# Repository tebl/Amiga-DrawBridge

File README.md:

# Amiga DrawBridge and Greaseweazle
I started this project out of fascination after reading a series of articles written by Rob Smith for the Amiga Addict magazine, detailing his solution for reading and writing Amiga floppy disks using an Arduino. Many of the build-yourself solutions provided came with some caveats, so I tried to look for the combination that should be the easiest to assemble. Along the way I also learned about some of the other well known solutions, in particular the Greaseweazle created by Keir Fraser. While there are certainly more professional options available on the market, KryoFlux in particular comes to mind. For the rest of us that want to make backups of our personal disks, I think that using these could be a fun little diversion into the world of backups.

- [1> Amiga DrawBridge](#1-amiga-drawbridge)
  - [1.1> Modules](#11-modules)
- [2> Greaseweazle](#2-greaseweazle)
  - [2.1> Modules](#21-modules)

## 1> Amiga DrawBridge
Rob Smith called his solution the **Arduino Amiga Floppy Disk Reader/Writer**, colloquially known as the **DrawBridge**. Completely open solution created with the Arduino as a starting point, all of the [information](http://amiga.robsmithdev.co.uk/instructions/promini) that you'd need to build it can be found on his [homepage](http://amiga.robsmithdev.co.uk/). You don't need more than few relatively common modules and a ton of wires to make it all work - so don't feel like this is something that you have to do in order to get started. These PCBs exists because I enjoy drawing things, and an inherent distrust of the kind of cheap Dupont cables I find myself purchasing. So I made a PCB for soldering the components onto instead.

One of the more interesting features of the DrawBridge is that he has put together a modified version of WinUAE, allowing the emulator to work directly with your physical disks! He later ported the feature so that the same can be done with the Greaseweazle, pretty impressive stuff!

### 1.1> Modules
For the technical details as well as information regarding the modules included by this specific github project, consult the table below - follow the documentation links for build instructions, BOM and anything else of that sort.  Faceplates and any backplates listed are mainly decorative, allowing you to put together something similar to a case without actually requiring a 3d-printer. 

| Module               | Required  | Documentation | Order      |
| -------------------- | --------- | ------------- | ---------- |
| Amiga DrawBridge     |       Yes | [Documentation](https://github.com/tebl/Amiga-DrawBridge/tree/main/Amiga%20Drawbridge), [Firmware](https://github.com/tebl/Amiga-DrawBridge/blob/main/documentation/drawbridge_firmware.md)                  | [PCBWay](https://www.pcbway.com/project/shareproject/Amiga_DrawBridge_fade665c.html)
| Amiga DrawBridge FA1 | Optional faceplate | [Documentation](https://github.com/tebl/Amiga-DrawBridge/tree/main/faceplates/Amiga%20Drawbridge%20FA1) | [PCBWay](https://www.pcbway.com/project/shareproject/Amiga_DrawBridge_Faceplate_FA1_f181f9af.html)
| Amiga DrawBridge FA2 | Optional faceplate | [Documentation](https://github.com/tebl/Amiga-DrawBridge/tree/main/faceplates/Amiga%20Drawbridge%20FA2) | [PCBWay](https://www.pcbway.com/project/shareproject/Amiga_DrawBridge_Faceplate_FA2_89c6eb36.html)
| Amiga DrawBridge BA1 | Optional backplate | [Documentation](https://github.com/tebl/Amiga-DrawBridge/tree/main/faceplates/Amiga%20Drawbridge%20BA1) | PCBWay

## 2> Greaseweazle
The [Greaseweazle](https://github.com/keirf/Greaseweazle) is another well known low-cost solution for working with physical floppy disks, having been created by Keir Fraser (also the creator of the FlashFloppy-firmware for *Gotek*-drives). The difference from the *DrawBridge* is that instead of working like a disk controller, it instead attempts to read the raw magnetic flux layer from the disks. This process *could* allow damaged or disks of unknown origin to be imaged.

### 2.1> Modules
For the technical details as well as information regarding the modules included by this specific github project, consult the table below - follow the documentation links for build instructions, BOM and anything else of that sort.  Faceplates and any backplates listed are mainly decorative, allowing you to put together something similar to a case without actually requiring a 3d-printer. 

| Module               | Required  | Documentation | Order      |
| -------------------- | --------- | ------------- | ---------- |
| Greaseweazle         |       Yes | [Documentation](https://github.com/tebl/Amiga-DrawBridge/tree/main/Greaseweazle), [Firmware](https://github.com/tebl/Amiga-DrawBridge/blob/main/documentation/greaseweazle_firmware.md), [Getting started](https://github.com/tebl/Amiga-DrawBridge/blob/main/documentation/greaseweazle_basics.md)                                                    | [PCBWay](https://www.pcbway.com/project/shareproject/Greaseweazle_0ea657b2.html)
| Greaseweazle FA1     | Optional faceplate | [Documentation](https://github.com/tebl/Amiga-DrawBridge/tree/main/faceplates/Greaseweazle%20FA1)       | [PCBWay](https://www.pcbway.com/project/shareproject/Greaseweazle_Faceplate_FA1_816b583d.html)
| Greaseweazle BA1 | Optional faceplate | [Documentation](https://github.com/tebl/Amiga-DrawBridge/tree/main/faceplates/Greaseweazle%20FB1)           | [PCBWay](https://www.pcbway.com/project/shareproject/Greaseweazle_Faceplate_FB1_83a3ce18.html)

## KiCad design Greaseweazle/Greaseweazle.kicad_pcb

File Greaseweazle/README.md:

# Greaseweazle
The [Greaseweazle](https://github.com/keirf/Greaseweazle) is a well known solution for working with physical floppy disks, all within the comforts of a modern operating system. It was created Keir Fraser, also the creator of the Flash Floppy firmware for Gotek drives, as a low cost alternative to the professional-oriented backup solutions such as the KryoFlux. Given that I've combined a project for creating both a DrawBridge and Greaseweazle into one, it is would be natural to say a few words about the differences between the two.

While *DrawBridge* was originally created to work with a specific disk format for the *Commodore Amiga*, the *Greaseweazle* will instead work with the raw magnetic flux layer from the disks. This may allow you to archive damaged, or even disks from unknown sources, to be archived for prosperity. Note that this does not necessarily mean you can use the resulting files, for that you would need a suitable emulator or similar program that have the capability of understanding the magnetic data that was originally read from the disks.

- [1> Building the device](#1-building-the-device)
  - [1.1> Soldering it together](#11-soldering-it-together)
  - [1.2> Power considerations](#12-power-considerations)
  - [1.3> Modifying STM32](#13-modifying-stm32)
  - [1.4> Let there be light](#14-let-there-be-light)
  - [1.5> Amstrad components](#15-amstrad-components)
  - [1.6> Finishing touches](#16-finishing-touches)
- [2> Schematic](#2-schematic)
- [3> BOM](#3-bom)

# 1> Building the device
Building a device such as this assumes you have at least minor experience soldering things together, recommended is that you at the very least have access to a soldering station with adjustable temperature. If currently available, you should probably start with 60/40 rosin core solder as the lead-free alternatives tends to be a bit harder to work with.

With the equipment sorted, now comes the shopping - so head on over to the [BOM](#3-bom)-section for some information on what kind of components that you'll need. Note that with sites such as ebay, AliExpress and similar sites that sell cheap chinese components, you'll need to treat these as a suggested search term and look for something that matches the gallery pictures.

## 1.1> Soldering it together
The construction of this unit should be fairly straight-forward, just take your time in order to make sure everything goes into place - more or less straight. I usually recommend starting by having a good look at the PCBs, try to figure out where all of the listed components go and in which orientation they go in (all of this should be clearly marked on the silkscreen). 

I will usually try to install components sorted by their physical size, doing it this way means you'll have an easier time keeping everything from looking somewhat crooked. This is your board, your build and you want it perfect - don't you? If you said no, then please go sit in a corner and think hard about your answer because I worked very hard at creating this design for myself and whoever wants one.

Here we've started by soldering all of the resistors, ensuring that we're using the correct values in each position. Note that some of the resistors will have a value printed with an asterisk after it, you may need to change these specific values or skip them entirely.

*) The value of these resistors need to be matched with the kind of LEDs that you are going to install on the board. The values as suggested should give a comfortably dimmed light when used with modern frosted LEDs, but need to be increased when used with bright clear LEDs. If you have access to the datasheet that goes with your LEDs and the maths to go with it, feel free to perform the necessary calculations. When in doubt you could always leave them out, then try out various values when testing a mostly completed unit.

**) This only applies to R10, not featured in the current pictures as it was added in a later revision. This is a convenient spot to install a new THT resistor in case you need to fix a specific cloned STM32 *Blue Pill*, as mentioned in the [Greaseweazle FAQ](https://github.com/keirf/Greaseweazle/wiki/Troubleshooting-FAQ) as a workaround for a board not showing up as a USB device. Unless you've specifically run into this issue, then you should **NOT** install R10.

Next step is installing the single transistor, as well as two of the resistors this will invert the activity LED so that it only lights up when there is traffic. While we can actually buy 2n3904 with legs pre-bent to match the footprint, these are very expensive and it is easier to just bend out the legs for these ourselves - taking care to match the flat side to that of the silkscreen. The reason for doing it this way is to make it easier to solder it in for beginners such as myself.

At this point we've gone ahead and installed the pin headers that will eventually be used to hold the STM32 board as well as a 34-pin IDC for the floppy drive itself. There's also a spot for a 26-pin version of it the interface for use with Amstrad 3" disk drives, but as I do not own any physical disks and/or disk drives I've not had to a chance to test this out for myself. Though I prefer the keying provided by the IDC sockets, you can instead opt to use standard dual-row pin headers here instead. 

## 1.2> Power considerations
Simple USB devices such as the various MCU boards are usually limited to a current draw of only **500mA**, plenty for doing small projects based on microcontrollers such as Arduino, STM32 and similar along with a handful of modern components. However in this case we'll be attempting to connect up a physical floppy drive up to the device and the powerdraw might easily surpass this, though this *might* be enough when used with later notebook-style disk drives. During my own testing with several older 3.5" floppy drives this was nowhere near enough, leading the drive to get stuck in a reset-loop.

For that reason, I'll be powering the drive separately using a DC 5v center positive power supply connected via the barrel connector. JP1 has been shorted across pins 1-2, this will separate this power supply from that of the USB (power LED will reflect that of the drive itself as these are now separate). 

The power cable going to the drive was bought ready-made as these are still available on sites such as Aliexpress and similar (usually listed as floppy power splitter or something to that effect), cutting off whatever parts I didn't need. Some floppy drives may also require 12v for such as many of the 5.25" drives and older, for those the recommended route is connecting one of the larger 4 pin Molex connector to J4 and power the whole thing from a PSU that delivers both of these voltages. An assembly picture for a later point in the build process is shown below.

If you buy one of the commonly available kit for connecting SATA/PATA drives up to a system over USB, you can get PSU that goes along with that. It's common for the cable to have a red wire for 5v, yellow for 12 and black for ground, but if you dug something really old out of a closet it might be a good idea to check the wiring as things wasn't always quite as standardized as it is now.

**WARNING!** The Amstrad 3-inch disk drives have the 5v and 12v wires swapped, connecting the drives to the floppy power connector as shown will instantly kill it. Have a read through of [1.5> Amstrad components](#15-amstrad-components) if you need to work with these drives, the short story is that you need to add a second modified power cable for these specific drives. 

## 1.3> Modifying STM32

This is more or less just a cosmetic thing, mainly because the boot jumpers on the standard *blue pill* make it a bit too tall to be used with a faceplate. Before we get too far ahead of ourselves and doing any actual work with the board, it might be wise to do some preliminary tests to make sure that the board you have is one of those that can be considered "*functional*" - because unfortunately there are quite a lot of boards that simply will not work properly! For that reason I suggest that you follow most of the [Greaseweazle Firmware](https://github.com/tebl/Amiga-DrawBridge/blob/main/documentation/greaseweazle_firmware.md) document, at least to ensure that it passes the "*blinky*"-test. 

Now that we've determined that we have a working board, we can get started on those modifications mentioned. If you have access to a desoldering station or simply a desoldering pump, you can just simply remove the 6pin header from the board and add a couple of pieces of wires in their place.

If you don't want to through the trouble of removing components, then an alternative is just to use a pair of pliers and pull off the plastic part of it (with a bit of force). Then cut off the part of the pins we don't need, either solder a piece of wire across the top as above to short them as expected - or you could just shorten the pins and bend them into contact with eachother, then add a bit of solder to ensure good contact.

When satisfied with the results, go ahead and solder the board into place on the main PCB.

## 1.4> Let there be light
Missing so far is the actual LEDs, which'll need a bit of vertical adjustment after installing some 10mm nylon hex standoffs. Your standard 5mm LEDs won't be quite that tall, so the suggestion is to put the LEDs into place (longer pin goes in the round hole) and then install the faceplate on top (without soldering any of the pins).

Start by soldering one of the pins, then reheat while pushing the LED firmly into the cutout on the faceplate. When satisfied that the results look good, you can solder the remaining pin as well as do a touch-up on the first one to ensure good connection. Shown below is where we should be at this point in the installation, keep on reading if you require support for 3 inch Amstrad drives as found on ZX Spectrum +3 and later Amstrad CPC computers (664 and 6128) - otherwise just skip ahead to [finishing touches](#16-finishing-touches).

## 1.5> Amstrad components
The Greaseweazle board also has a 26-pin option for connecting a 3 inch disk drive, commonly found installed in later Amstrad-produced machines such as the Sinclair ZX Spectrum +3, Amstrad CPC 664 and 6128 as well as some external disk disk drive options such as the FD-1 (needs to have internal power cable disconnected). All of these had single-sided drives, it is also the only configuration that I've had the chance to test.

Here we've gone ahead and installed the 26-pin connector as well as the 3-pin header, ensuring that we set it according to the type of drive we have available. The cable I'm using was ordered as a 26-pin ribbon cable off AliExpress without a cable twist, but before you can even consider connecting a drive up to the board we need to have a chat about safety.

**WARNING!** The Amstrad drives have a power connector that have been reversed, at least when compared to the later PC drives that we've become more familiar in the time since the 3 inch disk drives fell into obscurity (even though it shares the same connector). Connecting an unmodified floppy power connector into one of the drives will instantly kill your drive! 

To handle this you can consider just picking up a cheap splitter cable from AliExpress or similar sources, we'll then need to reverse the red and yellow cable on it - remembering to mark it specifically as being for Amstrad drives only. This is done by using a needle to slightly press in the little metal hooks on these two cables and pull out the cable, carefully bend the little hook back out again before reinserting the cable into the correct position [for Amstrad drives]. If you can't find a splitter with the male connector, you can always just split together two sets of cables when soldering them to the board - personally I prefer to have it detachable as this feature would rarely be used.

**NB!** As already mentioned in less than direct terms, I've not tested this solution with dual-sided drives. According to my mediocre Googling skills these drives were found on the Amstrad PCW line of computers, but as I lack a suitable drive and the corresponding disks to test things out I can't test it.

## 1.6> Finishing touches
If you still haven't installed the Greaseweazle firmware on the device, refer to [Greaseweazle Firmware](https://github.com/tebl/Amiga-DrawBridge/blob/main/documentation/greaseweazle_firmware.md) document for information on getting that done now. With the firmware in place, you can now finally connect up the drive and the device itself up to your computer using the Micro USB port (remember to power the drive via the barrel jack or molex, if needed).

The supplied software is easy to use for anyone with a passing familiarity with comand-line utilities, but I've put together a separate document on the [basics](https://github.com/tebl/Amiga-DrawBridge/blob/main/documentation/greaseweazle_basics.md) of actually using it.

# 2> Schematic
The supplied KiCad files should be sufficient as both a schematic and as a  starting point for ordering PCBs (basically you could just zip the contents of the export folder and upload that on a fabrication site), the schematic is also available in [PDF-format](https://github.com/tebl/Amiga-DrawBridge/tree/main/documentation/schematic) and this is what you'll need to print and work your way through this things don't work as expected after assembly.

# 3> BOM
Most parts should be easy to get a hold of from your favourite local electronic component shop, but given that I don't have access to such shops where I live so everything was based on whatever I could get cheapest from eBay/AliExpress (free shipping, but plan on waiting 3-4 weeks for delivery). Components in parenthesis can be considered optional for features beyond the more basic functionality, but where's the fun in that? You deserve the complete package.

| Reference             | Item                                                              | Count | Order  |
| --------------------- | ----------------------------------------------------------------- | ----- | ------ |
| Interface PCB         | Fabricate using Gerber files                                      |     1 | [PCBWay](https://www.pcbway.com/project/shareproject/Greaseweazle_0ea657b2.html)
| Faceplate PCB *       | Fabricate using Gerber files                                      |    (1)| [PCBWay](https://www.pcbway.com/project/shareproject/?tag=Greaseweazle%20Faceplates)
| A1                    | STM32F103C8T6 board (*blue pill*)                                 |     1 |
| D1,D2                 | 5mm LED, preferably one that is frosted                           |    (2)|
| J1 **                 | 2x17 pin male IDC socket                                          |     1 |
| J2                    | 2.1mm x 5.5mm barrel plug                                         |    (1)|
| J6 **                 | 2x13 pin male IDC socket                                          |    (1)|
| Q1                    | 2N3904 transistor (TO-92)                                         |    (2)|
| R1                    | 10k ohm resistor                                                  |    (1)|
| R2 ***                | 1k ohm resistor                                                   |    (1)|
| R3 ***                | 100 ohm resistor                                                  |    (1)|
| R4                    | 1k ohm resistor                                                   |    (1)|
| R5,R6,R7,R8           | 1k ohm resistor                                                   |     4 |
| R10 ****              | 1.5k ohm resistor (only install if explicitly need)               |    (1)|
| Mounting *****        | Nylon M3 hex standoffs 6mm (M-F)                                  |    (4)|
| Mounting *****        | Nylon M3 hex standoffs 8mm (M-F)                                  |    (4)|
| Mounting *****        | Nylon M3x6mm nylon screws                                         |    (4)|
| Floppy PSU cable      | 4 pin floppy connector with cable                                 |     1 |

*) Check out [faceplate](https://github.com/tebl/Amiga-DrawBridge/tree/main/faceplates) section of this repository or [PCBWay shared projects](https://www.pcbway.com/project/shareproject/?tag=Greaseweazle) for available options.

**) Components listed are for keyed IDC connector sockets, if you want to go with a cheaper option that is probably already in a box somewhere in your workshop - use standard dual-row pin breakable headers.

***) As detailed in the build notes, you may need to adjust these to match the type of LED you are installing. As long as you aren't installing the clear bright LEDs you should shouldn't have to change these except for preferences. Do the math if you have the correct datasheets and know how to do them, I find it easier to just throw something in there and see what happens.

****) Footprint for R10 provided as a spot for installing new resistor if the specific *Blue Pill* clone needs it and the original has been removed from the board, consult [Greaseweazle FAQ](https://github.com/keirf/Greaseweazle/wiki/Troubleshooting-FAQ) for more information. If unsure, do **NOT** install it.

*****) These are used in various places of the project. You can usually find some kits for M3 nylon standoffs, for the 6mm hex standoffs used on the bottom I've just cut off the screw part of it.

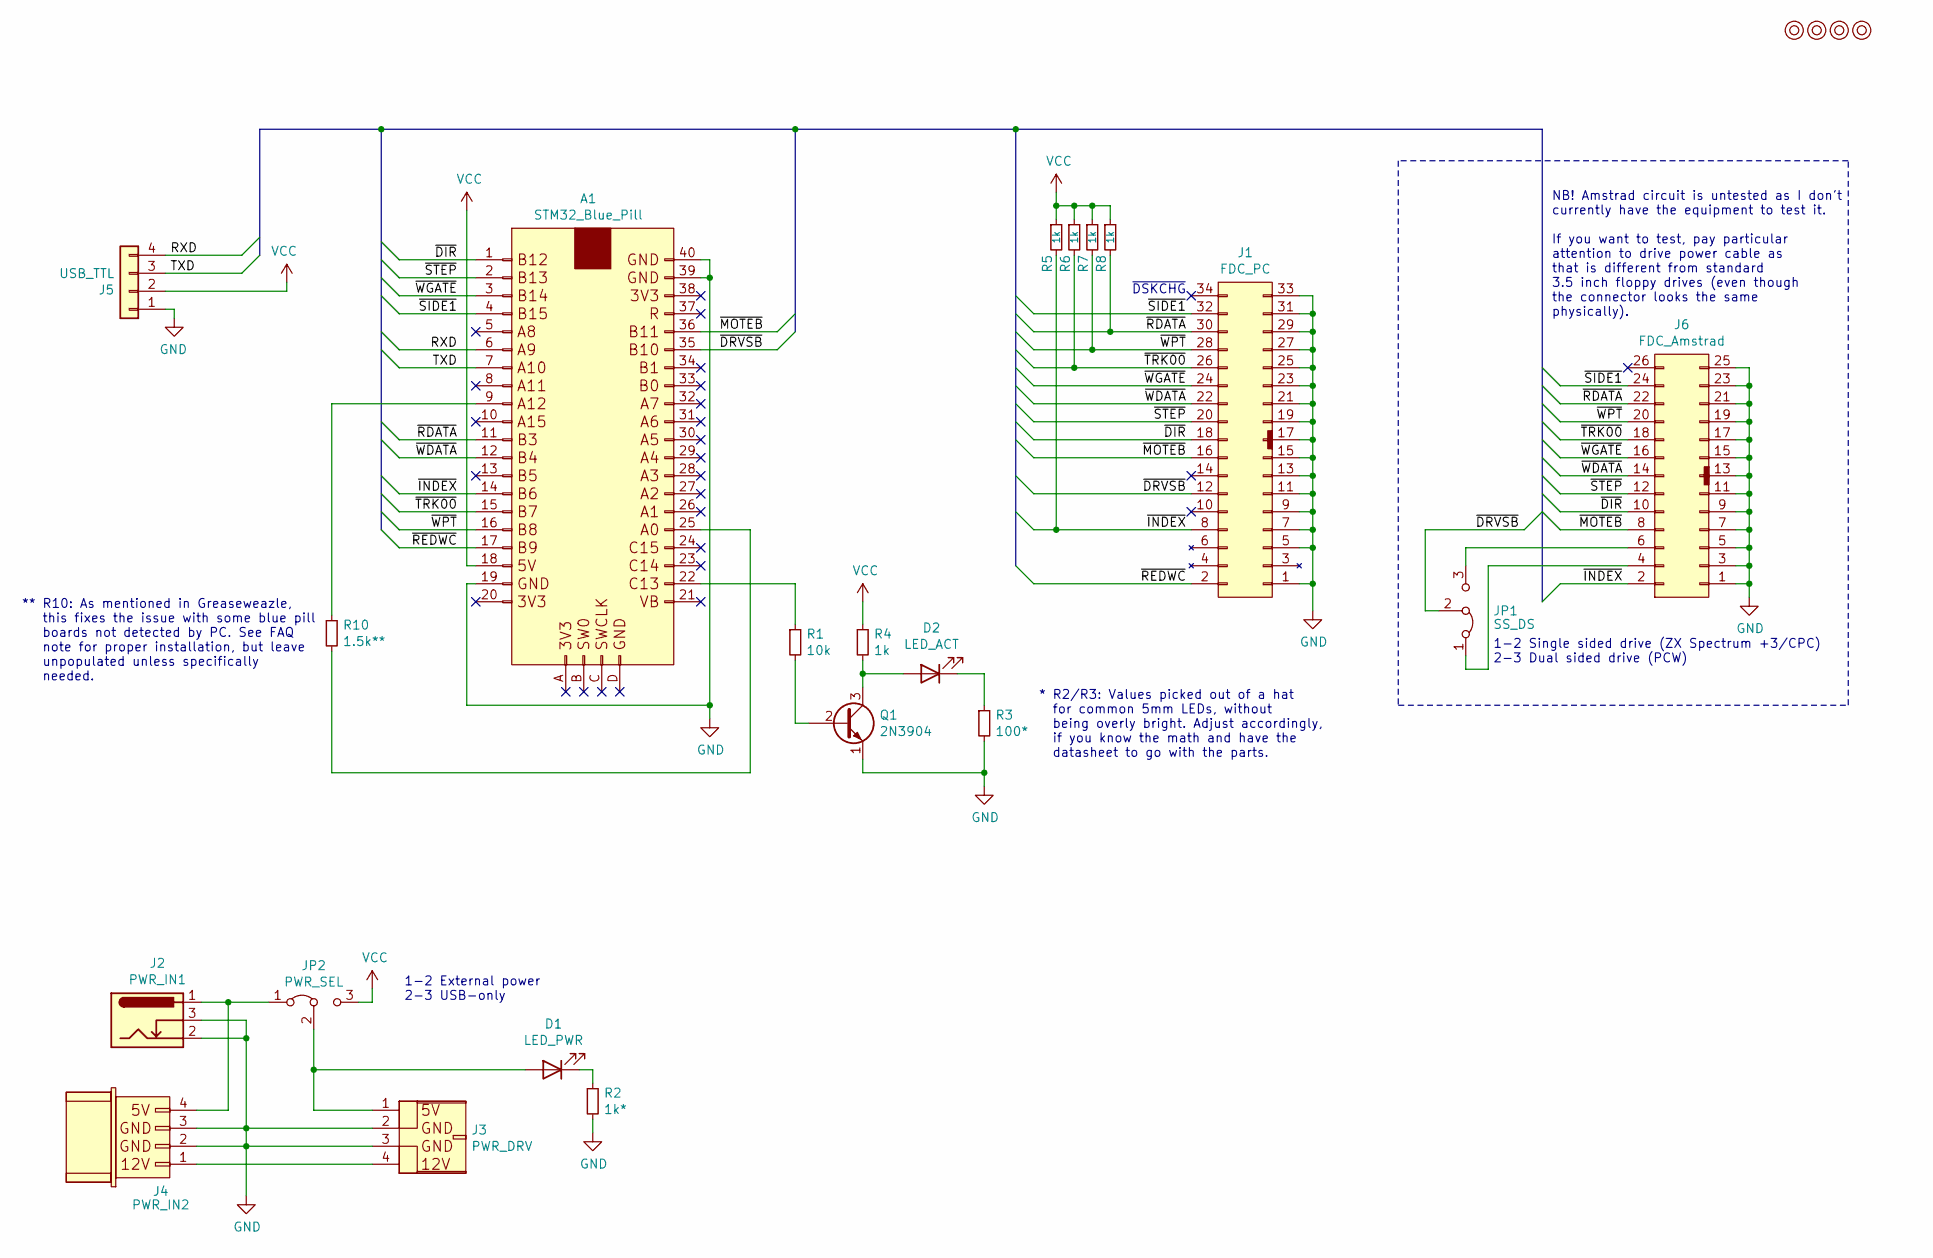
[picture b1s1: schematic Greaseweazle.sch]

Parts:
A1: STM32_Blue_Pill
D1: LED_PWR; LED_D5.0mm
D2: LED_ACT; LED_D5.0mm
J1: FDC_PC; IDC-Header_2x17_P2.54mm_Vertical
J2: PWR_IN1; BarrelJack_Horizontal
J3: PWR_DRV
J4: PWR_IN2; PWR_IN
J5: USB_TTL; PinHeader_1x04_P2.54mm_Horizontal
J6: FDC_Amstrad; IDC-Header_2x13_P2.54mm_Vertical
JP1: SS_DS; PinHeader_1x03_P2.54mm_Vertical
JP2: PWR_SEL; select
M1, M2, M3, M4: Mounting; M3_pin
Q1: 2N3904; TO-92_Inline_Wide
R1: 10k; R_Axial_DIN0207_L6.3mm_D2.5mm_P10.16mm_Horizontal
R2: 1k*; R_Axial_DIN0207_L6.3mm_D2.5mm_P10.16mm_Horizontal
R3: 100*; R_Axial_DIN0207_L6.3mm_D2.5mm_P10.16mm_Horizontal
R4, R5, R6, R7, R8: 1k; R_Axial_DIN0207_L6.3mm_D2.5mm_P10.16mm_Horizontal
R10: 1.5k**; R_Axial_DIN0207_L6.3mm_D2.5mm_P10.16mm_Horizontal

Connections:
/RXD: A1.6 (A9), J5.4
/TXD: A1.7 (A10), J5.3
/~DIR: A1.1 (B12), J1.18 (/DIR), J6.10 (/MOTEA)
/~DRVSB: A1.35 (B10), J1.12 (/DRVSB), JP1.2 (C)
/~INDEX: A1.14 (B6), J1.8 (/INDEX), J6.2 (/REDWC), R5.2
/~MOTEB: A1.36 (B11), J1.16 (/MOTEB), J6.8 (/INDEX)
/~RDATA: A1.11 (B3), J1.30 (/RDATA), J6.22 (/WDATA), R8.2
/~REDWC: A1.17 (B9), J1.2 (/REDWC)
/~SIDE1: A1.4 (B15), J1.32 (/SIDE1), J6.24 (/WGATE)
/~STEP: A1.2 (B13), J1.20 (/STEP), J6.12 (/DRVSB)
/~TRK00: A1.15 (B7), J1.26 (/TRK00), J6.18 (/DIR), R6.2
/~WDATA: A1.12 (B4), J1.22 (/WDATA), J6.14 (/DRVSA)
/~WGATE: A1.3 (B14), J1.24 (/WGATE), J6.16 (/MOTEB)
/~WPT: A1.16 (B8), J1.28 (/WPT), J6.20 (/STEP), R7.2
GND: A1.19 (GND), A1.39 (GND), A1.40 (GND), J1.1 (GND), J1.5 (GND), J1.7 (GND), J1.9 (GND), J1.11 (GND), J1.13 (GND), J1.15 (GND), J1.17 (GND), J1.19 (GND), J1.21 (GND), J1.23 (GND), J1.25 (GND), J1.27 (GND), J1.29 (GND), J1.31 (GND), J1.33 (GND), J2.2, J2.3, J3.2, J3.3, J4.2, J4.3, J5.1, J6.1 (GND), J6.3 (KEY), J6.5 (GND), J6.7 (GND), J6.9 (GND), J6.11 (GND), J6.13 (GND), J6.15 (GND), J6.17 (GND), J6.19 (GND), J6.21 (GND), J6.23 (GND), J6.25 (GND), Q1.1 (E), R2.2, R3.2
unnamed: A1.9 (A12), R10.1
unnamed: A1.22 (C13), R1.1
unnamed: A1.25 (A0), R10.2
unnamed: D1.1 (K), R2.1
unnamed: D1.2 (A), J3.1, JP2.2 (C)
unnamed: D2.1 (K), R3.1
unnamed: D2.2 (A), Q1.3 (C), R4.2
unnamed: J2.1, J4.4, JP2.1 (A)
unnamed: J3.4, J4.1
unnamed: J6.4 (nc), JP1.1 (A)
unnamed: J6.6 (nc), JP1.3 (B)
unnamed: Q1.2 (B), R1.2
VCC: A1.18 (5V), J5.2, JP2.3 (B), R4.1, R5.1, R6.1, R7.1, R8.1

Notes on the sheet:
1-2 External power 2-3 USB-only
* R2/R3: Values picked out of a hat for common 5mm LEDs, without being overly bright. Adjust accordingly, if you know the math and have the datasheet to go with the parts.
~DSKCHG
NB! Amstrad circuit is untested as I don't currently have the equipment to test it. If you want to test, pay particular attention to drive power cable as that is different from standard 3.5 inch floppy drives (even though the connector looks the same physically).
1-2 Single sided drive (ZX Spectrum +3/CPC) 2-3 Dual sided drive (PCW)
** R10: As mentioned in Greaseweazle, this fixes the issue with some blue pill boards not detected by PC. See FAQ note for proper installation, but leave unpopulated unless specifically needed.

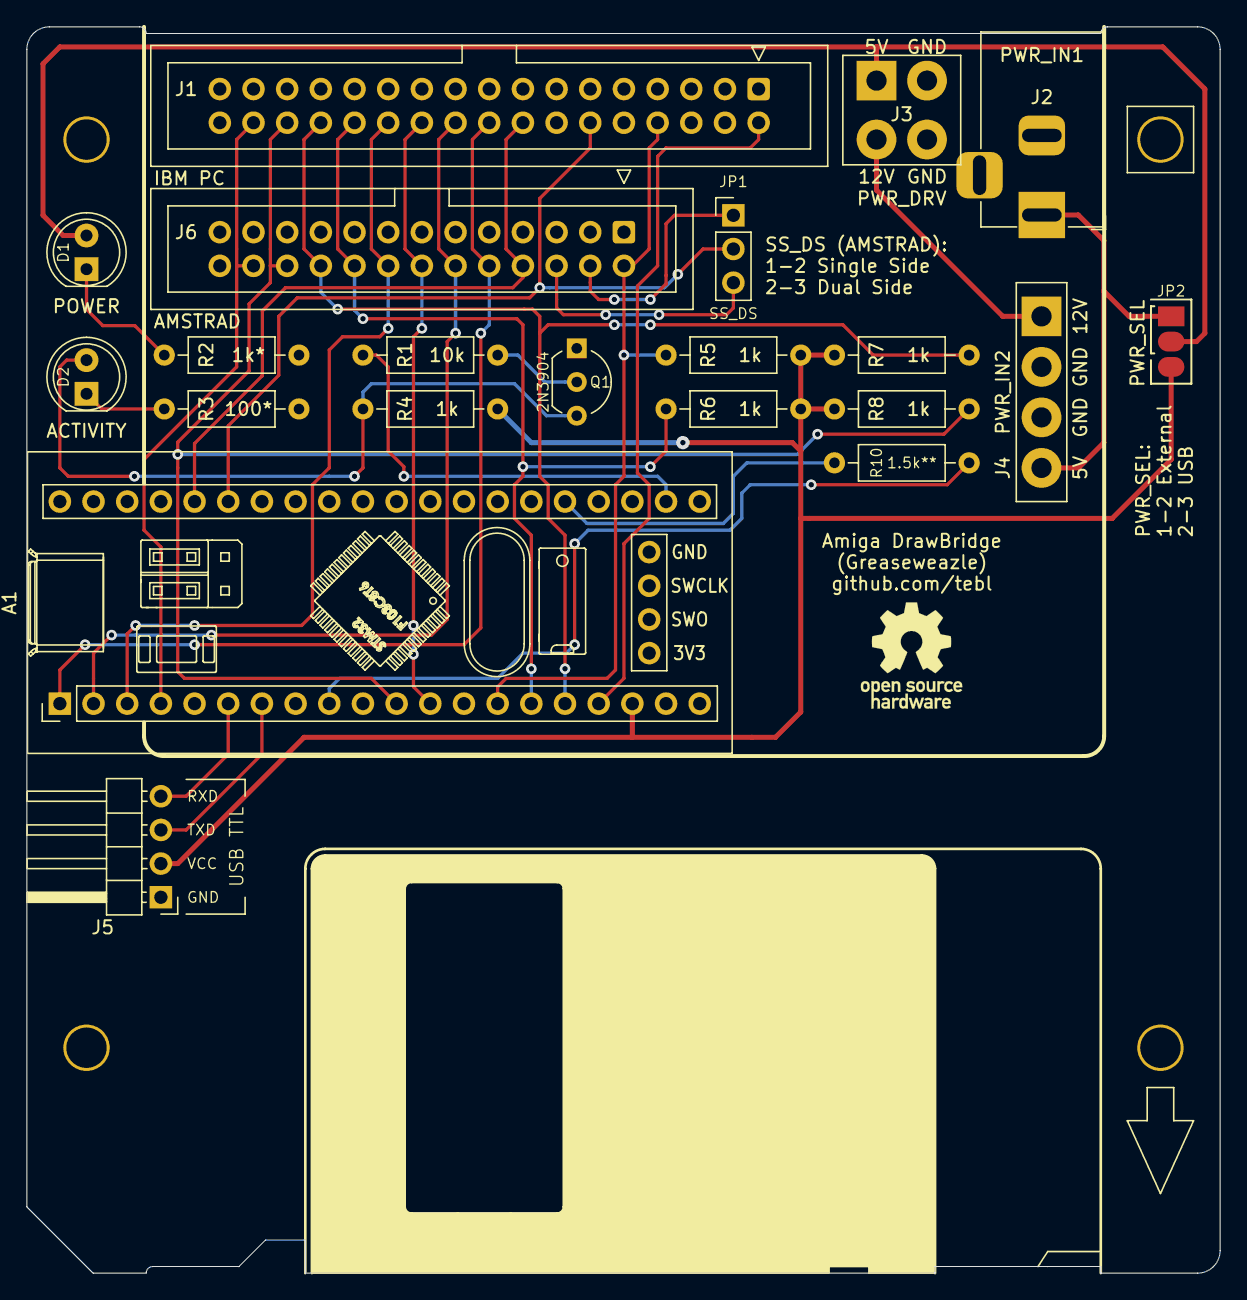
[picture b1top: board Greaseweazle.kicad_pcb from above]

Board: 2 copper layers, 90.0 x 94.0 mm, 25 parts (0 on the bottom side), 28 nets.

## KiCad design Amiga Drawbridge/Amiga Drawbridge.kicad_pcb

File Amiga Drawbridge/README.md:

# Amiga DrawBridge
I first read about the Amiga DrawBridge in a series of articles in the *Amiga Addict*-magazine, a device created by Rob Smith for reading and writing Commodore Amiga floppy disks using a modern computer. Because I like drawing things more than probably actually using it, I designed my own PCB around the details available from the creators [homepage](http://amiga.robsmithdev.co.uk/). You strictly don't even need a PCB, several options are described on the same page - some of them can be put together without owning a soldering iron. The goal for my design was to put together something that looks nice, but opting for solutions that should be easy for anyone to solder together.

- [1> Building the device](#1-building-the-device)
  - [1.1> Soldering it together](#11-soldering-it-together)
  - [1.2> Power considerations](#12-power-considerations)
  - [1.3> Modifying FTDI-adapter](#13-modifying-ftdi-adapter)
  - [1.4> Install Arduino Pro Mini](#14-install-arduino-pro-mini)
  - [1.5> Let there be light](#15-let-there-be-light)
  - [1.6> Finishing touches](#16-finishing-touches)
- [2> Schematic](#2-schematic)
- [3> BOM](#3-bom)

# 1> Building the device
Building a device such as this assumes you have at least minor experience soldering things together, recommended is that you at the very least have access to a soldering station with adjustable temperature. If currently available, you should probably start with 60/40 rosin core solder as the lead-free alternatives tends to be a bit harder to work with.

With the equipment sorted, now comes the shopping - so head on over to the [BOM](#3-bom)-section for some information on what kind of components that you'll need. Note that with sites such as ebay, AliExpress and similar sites that sell cheap chinese components, you'll need to treat these as a suggested search term and look for something that matches the gallery pictures.

## 1.1> Soldering it together
The construction of this unit should be fairly straight-forward, just take your time in order to make sure everything goes into place - more or less straight. I usually recommend starting by having a good look at the PCBs, try to figure out where all of the listed components go and in which orientation they go in (all of this should be clearly marked on the silkscreen). 

I will usually try to install components sorted by their physical size, doing it this way means you'll have an easier time keeping everything from looking somewhat crooked. This is your board, your build and you want it perfect - don't you? If you said no, then go sit in the corner because I worked hard on creating this for myself and whoever wants to build one.

Here we've started by soldering all of the resistors, ensuring that we're using the correct values in each position. Note that two of the resistors will have a value printed with an asterisk, this is because their values would normally need to be matched with the kind of LEDs that you will install on the board. The suggested values should give a comfortable dimmed light when used with modern frosted LEDs, but will definitely be on the lower side of things when used with clear bright LEDs. If you have access to the datasheet that goes with your LEDs and the maths to go with it, perform the necessary calculations - or just accept the values as given (which should work in most cases).

Second, I've started by installing the pin headers used to attach the two modules to the main PCB, taking care to only pins where they are needed (some Pro Mini clones will not have all of these present). In order to ensure that everything fits together later, consider soldering in just one of the pins of each row - then reheat and adjust so that they sit flush with the board.

The 34-pin IDC connector for the floppy drive is the next thing that should go into place, it has the same height as the pin headers installed in the previous so it should align itself somewhat. Though I prefer the keying provided when using proper IDC sockets, you can instead opt to just use standard dual-row pin headers here. 

## 1.2> Power considerations
Simple USB devices such as the various MCU boards is oftenly limited to a 500mA current draw, most commonly this is plenty for doing small projects based on microcontrollers such as the Arduino along with a handful of components. However in this case we'll be connecting up a physical floppy drive up to the device, though this *may* be enough when used with later notebook-style drives - it wasn't when I tested it with my earlier 3.5" internal floppy drives.

![
Build 004](https://github.com/tebl/Amiga-DrawBridge/raw/main/gallery/drawbridge_build_004.jpg)

For that reason, I'll be powering the drive separately using a DC 5v center positive power supply connected via the barrel connector. JP2 has been shorted across pins 1-2 to reflect this, this will separate this power supply from that of the USB (power LED will reflect that of the drive itself as these are now separate). 

The power cable going to the drive was bought ready-made as these are still available on sites such as Aliexpress and similar (usually listed as floppy power splitter or something to that effect), cutting off whatever parts I didn't think I'd need.

Some floppy drives may also require 12v for such as many of the 5.25" drives and older, for those the recommended route is connecting one of the larger 4 pin Molex connector to J4 and power the whole thing from a PSU that delivers both of these voltages. If you buy one of the commonly available kit for connecting SATA/PATA drives up to a system over USB, you can get PSU that goes along with that. It's common for the cable to have a red wire for 5v, yellow for 12 and black for ground, but if you dug something really old out of a closet it might be a good idea to check the wiring as things wasn't always quite as standardized as it is now.

**NB!** The final revision of this PCB has moved around some of the pads used for connecting the cables, so make sure to connect them according to the markings on **your** board instead of copying the images shown here. To re-iterate: 5v is red, 12v is yellow and both black cables are for ground. 

## 1.3> Modifying FTDI-adapter
This is more or less just a cosmetic thing, mostly because the pin headers on top of it will be too tall when installing the faceplates - neither does it make much sense to have it configurable to the end user since the other setting will simply make things stop working. The process is simple, just remove the jumper cap, pull off the black plastic part and then pull out each of the pins. Clean up the holes with some solder wich and solder some of the resistor clippings across the correct two pins as shown below.

If you don't want to through the trouble of removing components, then a somewhat different alternative is to just to use a pair of pliers and pull off the plastic part of it (with a bit of force) as described earlier. Cut off the part of the pins we don't need, then add solder between the two trimmed pins until they make contact. For once we've intentionally created a solder bridge.

When satisfied with the results, go ahead and solder the board into place on the main PCB.

## 1.4> Install Arduino Pro Mini

The Arduino is soldered to the board without much needed other than making sure that the orientation of the board matches the one illustrated on the silkscreen. There are however a few variations of boards on the market though most of these seem to have the reset button in more or less space, but we need to set JP1 according to the specific variation of board we have. Looking at the pin that is now on the top-right corner, if this is marked DTR then we need to bridge pins 1-2 on JP1.

## 1.5> Let there be light
Missing so far are the actual LEDs, which'll need a bit of vertical adjustment after installing some 10mm nylon hex standoffs. Your standard 5mm LEDs won't be quite that tall, so the suggestion is to put the LEDs into place (longer pin in the round hole) and then install the faceplate on top (without actually soldering in any of the pins).

Start by soldering one of the pins, then reheat while pushing the LED firmly into the cutout on the faceplate. When satisfied that the results look good, you can solder the remaining pin as well as do a touch-up on the first one to ensure good connection.

## 1.6> Finishing touches

The last step that we need to do is install the firmware onto the Arduino Pro Mini, this is described in a separate [document](https://github.com/tebl/Amiga-DrawBridge/blob/main/documentation/drawbridge_firmware.md). With the firmware in place, you can now finally connect up the drive and the device itself up to your computer using the Micro USB port (remember to power the drive via the barrel jack, if needed).

# 2> Schematic
The supplied KiCad files should be sufficient as both a schematic and as a  starting point for ordering PCBs (basically you could just zip the contents of the export folder and upload that on a fabrication site), the schematic is also available in [PDF-format](https://github.com/tebl/Amiga-DrawBridge/tree/main/documentation/schematic) and this is what you'll need to print and work your way through this things don't work as expected after assembly.

# 3> BOM
Most parts should be easy to get a hold of from your favourite local electronic component shop, but given that I don't have access to such shops where I live so everything was based on whatever I could get cheapest from eBay/AliExpress (free shipping, but plan on waiting 3-4 weeks for delivery). Components in parenthesis can be considered optional for features beyond the more basic functionality, but where's the fun in that? You deserve the complete package.

| Reference             | Item                                                              | Count | Order  |
| --------------------- | ----------------------------------------------------------------- | ----- | ------ |
| Interface PCB         | Fabricate using Gerber files                                      |     1 | [PCBWay](https://www.pcbway.com/project/shareproject/Amiga_DrawBridge_fade665c.html)
| Faceplate PCB *       | Fabricate using Gerber files                                      |    (1)| [PCBWay](https://www.pcbway.com/project/shareproject/?tag=Amiga%20DrawBridge%20Faceplates)
| A1                    | Arduino Pro Mini                                                  |     1 |
| A2                    | FT232RL Module                                                    |     1 |
| D1,D2                 | 5mm LED, preferably one that is frosted                           |    (2)|
| J1 **                 | 2x17 pin male IDC socket                                          |     1 |
| J2                    | 2.1mm x 5.5mm barrel plug                                         |    (1)|
| R1                    | 1k ohm resistor                                                   |     1 |
| R2,R3 ***             | 330 ohm resistor                                                  |    (2)|
| Mounting ****         | Nylon M3 hex standoffs 6mm (M-F)                                  |    (4)|
| Mounting ****         | Nylon M3 hex standoffs 8mm (M-F)                                  |    (4)|
| Mounting ****         | Nylon M3x6mm nylon screws                                         |    (4)|
| Floppy PSU cable      | 4 pin floppy connector with cable                                 |     1 |

*) Check out [faceplate](https://github.com/tebl/Amiga-DrawBridge/tree/main/faceplates) section of this repository or [PCBWay shared projects](https://www.pcbway.com/project/shareproject/?tag=DrawBridge) for available options.

**) Components listed are for keyed IDC connector sockets, if you want to go with a cheaper option that is probably already in a box somewhere in your workshop - use standard dual-row pin breakable headers.

***) As detailed in the build notes, you may need to adjust these to match the type of LED you are installing. As long as you aren't installing the clear bright LEDs you should shouldn't have to change these except for preferences. Do the math if you have the correct datasheets and know how to do them, I find it easier to just throw something in there and see what happens.

****) These are used in various places of the project. You can usually find some kits for M3 nylon standoffs, for the 6mm hex standoffs used on the bottom I've just cut off the screw part of it.

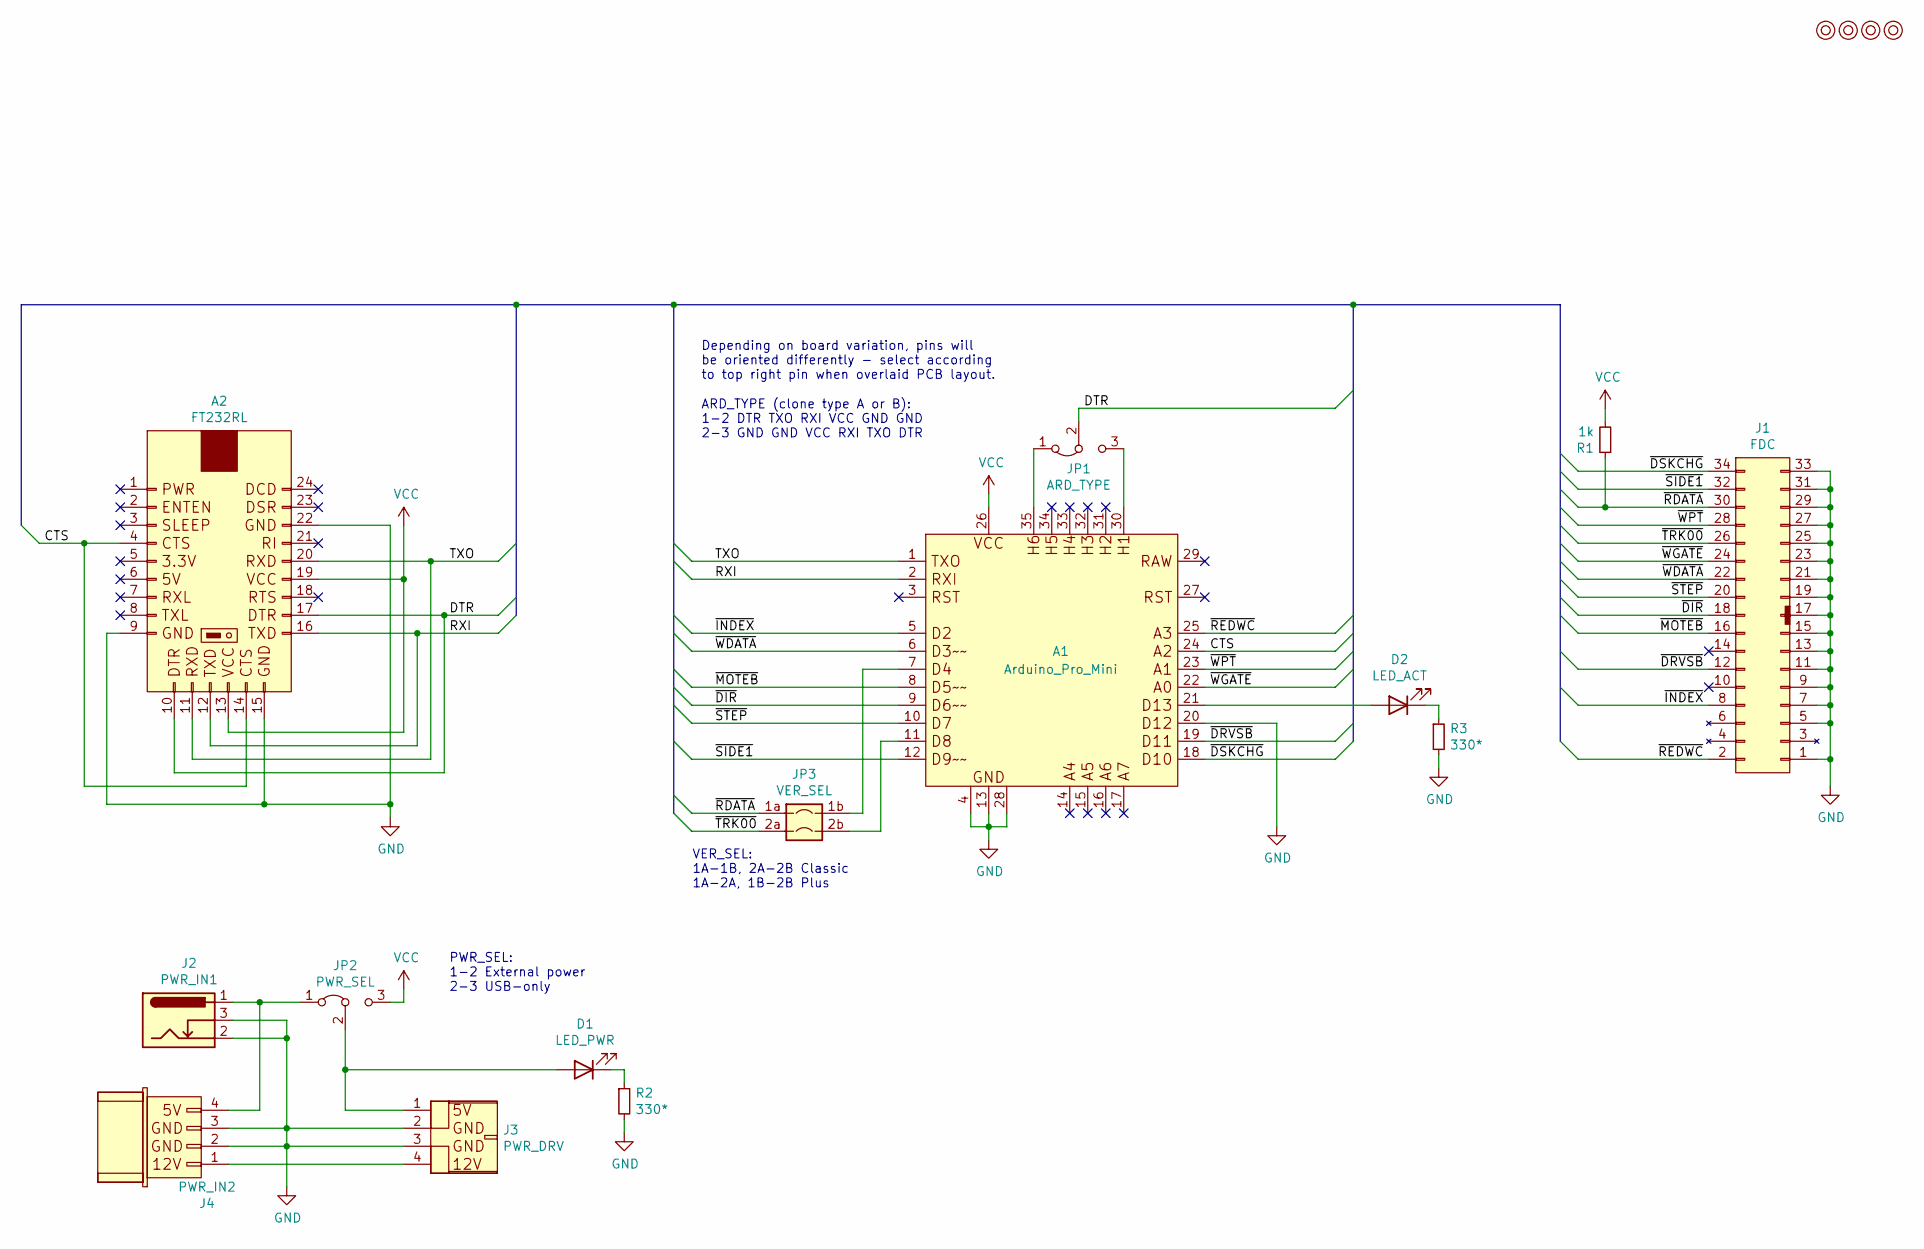
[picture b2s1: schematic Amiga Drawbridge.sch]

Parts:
A1: Arduino_Pro_Mini
A2: FT232RL
D1: LED_PWR; LED_D5.0mm
D2: LED_ACT; LED_D5.0mm
J1: FDC; IDC-Header_2x17_P2.54mm_Vertical
J2: PWR_IN1; BarrelJack_Horizontal
J3: PWR_DRV
J4: PWR_IN2; PWR_IN
JP1: ARD_TYPE; select
JP2: PWR_SEL; select
JP3: VER_SEL; select_swappable
M1, M2, M3, M4: Mounting; M3_pin
R1: 1k; R_Axial_DIN0207_L6.3mm_D2.5mm_P10.16mm_Horizontal
R2, R3: 330*; R_Axial_DIN0207_L6.3mm_D2.5mm_P10.16mm_Horizontal

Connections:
/CTS: A1.24 (A2), A2.4 (CTS), A2.14 (CTS)
/DTR: A2.10 (DTR), A2.17 (DTR), JP1.2 (C)
/RXI: A1.2 (RXI), A2.12 (TXD), A2.16 (TXD)
/TXO: A1.1 (TXO), A2.11 (RXD), A2.20 (RXD)
/~DIR: A1.9 (D6), J1.18 (/DIR)
/~DRVSB: A1.19 (D11), J1.12 (/DRVSB)
/~DSKCHG: A1.18 (D10), J1.34 (/DSKCHG)
/~INDEX: A1.5 (D2), J1.8 (/INDEX)
/~MOTEB: A1.8 (D5), J1.16 (/MOTEB)
/~RDATA: J1.30 (/RDATA), JP3.1a, R1.1
/~REDWC: A1.25 (A3), J1.2 (/REDWC)
/~SIDE1: A1.12 (D9), J1.32 (/SIDE1)
/~STEP: A1.10 (D7), J1.20 (/STEP)
/~TRK00: J1.26 (/TRK00), JP3.2a
/~WDATA: A1.6 (D3), J1.22 (/WDATA)
/~WGATE: A1.22 (A0), J1.24 (/WGATE)
/~WPT: A1.23 (A1), J1.28 (/WPT)
GND: A1.4 (GND), A1.13 (GND), A1.20 (D12), A1.28 (GND), A2.9 (GND), A2.15 (GND), A2.22 (GND), J1.1 (GND), J1.5 (GND), J1.7 (GND), J1.9 (GND), J1.11 (GND), J1.13 (GND), J1.15 (GND), J1.17 (GND), J1.19 (GND), J1.21 (GND), J1.23 (GND), J1.25 (GND), J1.27 (GND), J1.29 (GND), J1.31 (GND), J1.33 (GND), J2.2, J2.3, J3.2, J3.3, J4.2, J4.3, R2.2, R3.2
unnamed: A1.7 (D4), JP3.1b
unnamed: A1.11 (D8), JP3.2b
unnamed: A1.21 (D13), D2.2 (A)
unnamed: A1.30 (H1), JP1.3 (B)
unnamed: A1.35 (H6), JP1.1 (A)
unnamed: D1.1 (K), R2.1
unnamed: D1.2 (A), J3.1, JP2.2 (C)
unnamed: D2.1 (K), R3.1
unnamed: J2.1, J4.4, JP2.1 (A)
unnamed: J3.4, J4.1
VCC: A1.26 (VCC), A2.13 (VCC), A2.19 (VCC), JP2.3 (B), R1.2

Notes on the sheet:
PWR_SEL: 1-2 External power 2-3 USB-only
Depending on board variation, pins will be oriented differently - select according to top right pin when overlaid PCB layout.
ARD_TYPE (clone type A or B): 1-2 DTR TXO RXI VCC GND GND 2-3 GND GND VCC RXI TXO DTR
VER_SEL: 1A-1B, 2A-2B Classic 1A-2A, 1B-2B Plus

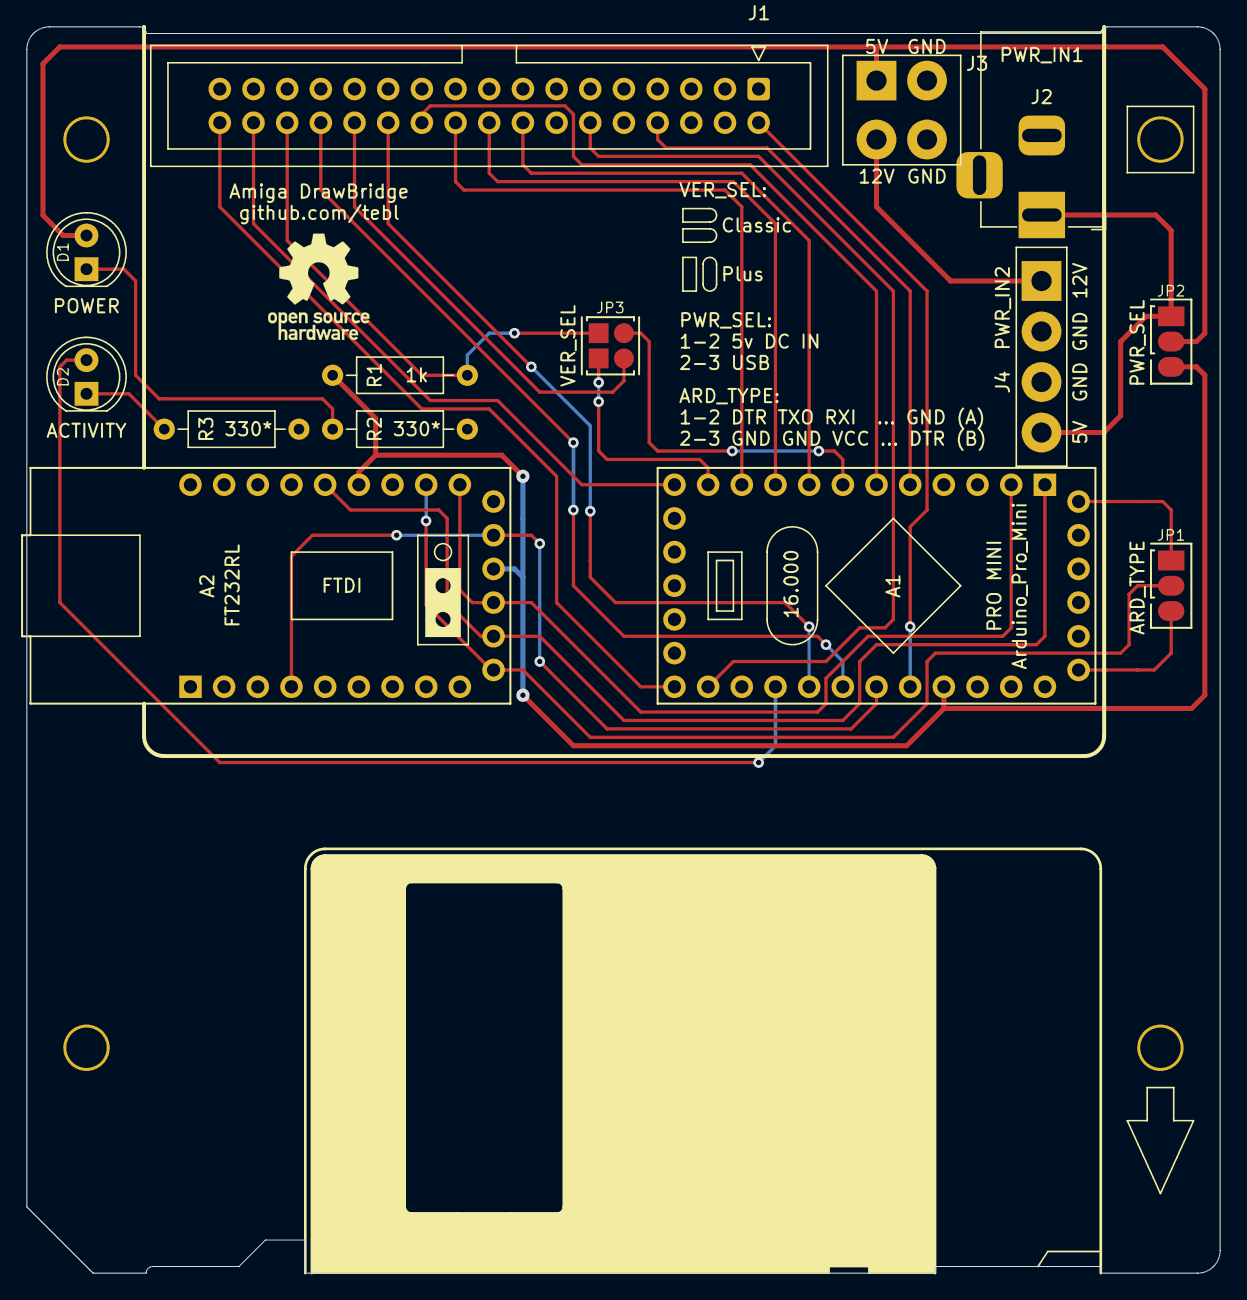
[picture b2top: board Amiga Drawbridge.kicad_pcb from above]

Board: 2 copper layers, 90.0 x 94.0 mm, 18 parts (0 on the bottom side), 29 nets.

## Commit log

2021-09-25 PCB outline
2021-09-26 Added schematic
2021-09-27 Added metal details
2021-09-27 Arduino Pro Mini footprint
2021-09-29 Routed tracks
2021-09-29 Exported files
2021-09-30 First version
2021-10-10 Added LEDs and moved connectors
2021-10-10 Exported Gerber files
2021-10-10 Backplate
2021-10-10 Faceplate
2021-10-10 Export files
2021-10-11 Changed made by notice
2021-10-11 Added images
2021-11-01 Greaseweazle using blue pill
2021-11-03 Fix silkscreen error
2021-11-03 Arduino settings
2021-11-03 Can swap D4 and D8
2021-11-03 Fixed silkscreen error
2021-11-03 Silkscreen tweaks
2021-11-04 Greaseweazle faceplate
2021-11-04 Greaseweazle faceplate with amstrad cutout
2021-11-04 Add previews
2021-11-04 Add build images
2021-11-05 Add some README details
2021-11-05 Text tweaks
2021-11-07 HitSquad style faceplate
2021-11-07 Preview
2021-11-10 Changed power pin order
2021-11-10 Add stm32 link images
2021-11-10 More screenshots
2021-11-10 Documenting things
2021-11-10 GW usage
2021-11-11 Usage details
2021-11-11 Screenshots
2021-11-11 gw getting started
2021-11-11 Invert activity LED
2021-11-11 Add images
2021-11-12 Gerber export and updated preview
2021-11-12 Some README files
2021-11-14 DrawBridge Firmware
2021-11-18 Add image
2021-11-18 Greaseweazle README
2021-11-18 Cable notice updated
2021-11-18 Updated image
2021-11-18 Add README
2021-11-18 Tweaked Amstrad pinout to match pins available (still untested)
2021-11-18 Changed README
2021-11-20 Tweaked silkscreen
2021-11-20 Change PWR_EXT2 power input to 4pin
2021-11-20 DKSCHG never actually connected to anything
2021-11-20 Added pullups
2021-11-22 Add R10 (in case it is needed)
2021-11-22 PWR_EXT2 renamed PWR_IN2, now 4 pin to match greaseweazle
2021-12-11 Add faceplate README
2021-12-11 Added asterisk
2021-12-11 Fixed link
2021-12-19 Updated build images
2021-12-19 Added documentation on how to update GW
2021-12-19 Added update to basics
2021-12-19 Updated build image
2021-12-30 Added PCBway links
2021-12-30 More URLs
2022-01-19 Update links after GW firmware was separated from the host tools
2022-01-19 Added Amstrad build details
2022-01-20 Amstrad details
2022-01-20 Add text commands
